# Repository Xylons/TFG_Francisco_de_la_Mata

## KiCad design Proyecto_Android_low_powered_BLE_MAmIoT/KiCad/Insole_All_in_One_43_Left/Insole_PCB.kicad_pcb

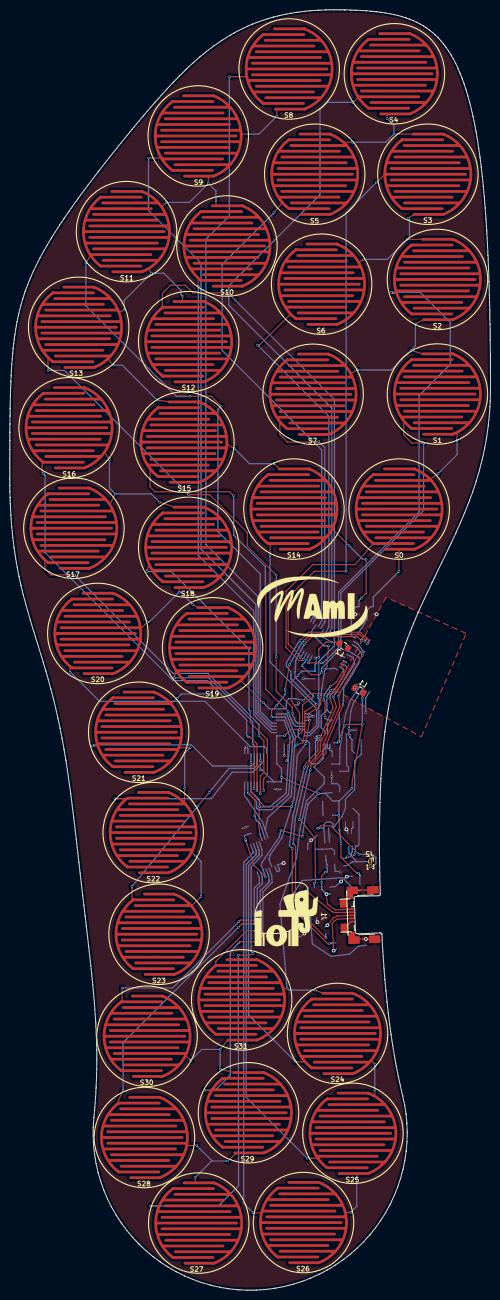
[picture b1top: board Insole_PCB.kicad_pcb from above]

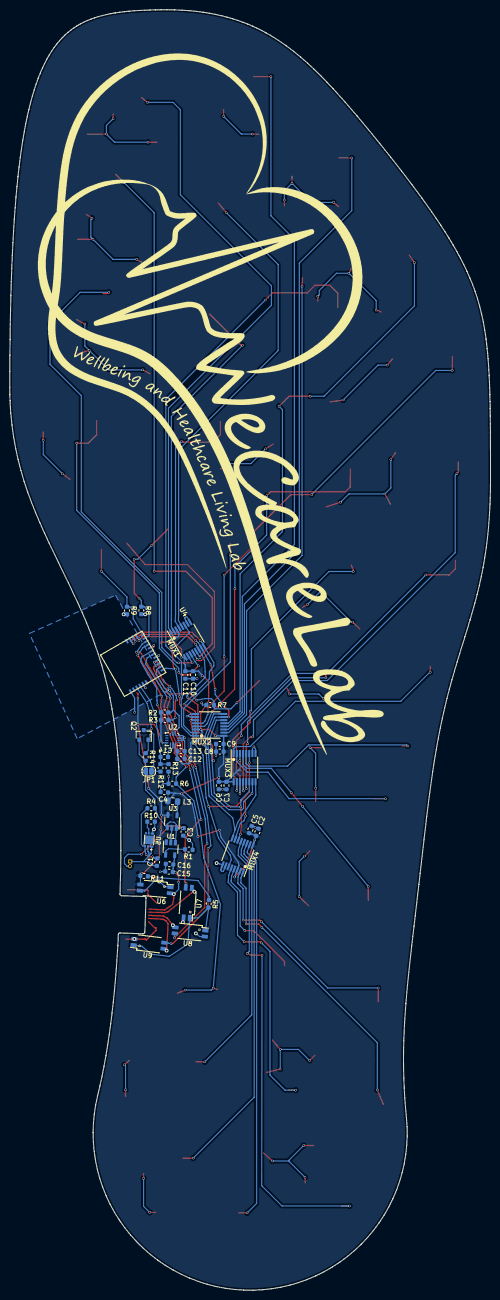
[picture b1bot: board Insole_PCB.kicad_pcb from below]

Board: 2 copper layers, 100.5 x 267.7 mm, 82 parts (46 on the bottom side), 65 nets.

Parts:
C1, C5, C7, C9, C11, C13, C14, C16: 0.1uF; C_0603_1608Metric
C2, C6, C8, C10, C12, C15: 1uF; C_0603_1608Metric
C3: 4.7uF; C_0603_1608Metric
C4: 10uF; C_0603_1608Metric
J1: Conn_Micro_USB; USB_Micro_CustomV2
J2: 3V7_Battery; PinHeader_1x02_P1.00mm_Vertical
JP1: Jumper_NO_Small; SolderJumper-2_P1.3mm_Open_RoundedPad1.0x1.5mm
L1, L2: 300ohm 100MHz; L_0805_2012Metric_Pad1.15x1.40mm_HandSolder
L3: 1uH; L_0805_2012Metric_Pad1.15x1.40mm_HandSolder
MUX1, MUX2, MUX3, MUX4: CD74HC4051; TSSOP-16_4.4x5mm_P0.65mm
Q2: Q_PMOS_GSD; SOT-23
R1, R2, R3, R6, R7, R8, R9, R12, R13: 10k; R_0603_1608Metric
R4: 390 ohm; R_0603_1608Metric
R5: 0-1k; R_0603_1608Metric
R10: 2.7k; R_0603_1608Metric
R11: 100-500 ohm; R_0603_1608Metric
R14: 100k; R_0603_1608Metric
S0, S1, S2, S3, S4, S5, S6, S7, S8, S9, S10, S11, S12, S13, S14, S15, S16, S17, S18, S19, S20, S21, S22, S23, S24, S25, S26, S27, S28, S29, S30, S31: FSR; FSR_Circle_9mm
U1: STC4054-4.2; TSOT-23-5
U2: ISM330DLC; Bosch_LGA-14_3x2.5mm_P0.5mm
U3: ADP2108AUJ-3.3; TSOT-23-5
U4: CYBLE-222014-01
U5: AP9211SA-AN-HAC-7; AP9211SAACHAC7
U6, U7, U8, U9: TCMT1100; SOP-4_4.4x2.8mm_P1.27mm

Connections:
+3V3: C2.2, C4.1, C5.2, C6.2, C7.2, C8.2, C9.2, C10.2, C11.2, C12.2, C13.2, L1.1, L2.1, L3.2, MUX1.3, MUX1.16, MUX2.3, MUX2.16, MUX3.3, MUX3.16, MUX4.3, MUX4.16, R2.1, R3.1, R11.2, U2.5, U2.8, U3.4, U6.4
+5V: C15.2, C16.2, J1.1, U1.4, U6.2
+BATT: C3.2, J2.2, JP1.2, Q2.2, R4.1, R14.1, U1.3, U3.1, U3.3
-BATT: C1.2, J2.1, U5.1, U5.2
/MUX_E: MUX1.6, MUX2.6, MUX3.6, MUX4.6, U4.7
/S0: MUX1.11, MUX2.11, MUX3.11, MUX4.11, U4.19
/S1: MUX1.10, MUX2.10, MUX3.10, MUX4.10, U4.20
/S2: MUX1.9, MUX2.9, MUX3.9, MUX4.9, U4.21
/U1_A0: MUX1.13, S0.2
/U1_A1: MUX1.14, S1.2
/U1_A2: MUX1.15, S2.2
/U1_A3: MUX1.12, S3.2
/U1_A4: MUX1.1, S4.2
/U1_A5: MUX1.5, S5.2
/U1_A6: MUX1.2, S6.2
/U1_A7: MUX1.4, S7.2
/U1_Data: R9.2, S0.1, S1.1, S2.1, S3.1, S4.1, S5.1, S6.1, S7.1, U4.18
/U2_A0: MUX2.13, S8.2
/U2_A1: MUX2.14, S9.2
/U2_A2: MUX2.15, S10.2
/U2_A3: MUX2.12, S11.2
/U2_A4: MUX2.1, S12.2
/U2_A5: MUX2.5, S13.2
/U2_A6: MUX2.2, S14.2
/U2_A7: MUX2.4, S15.2
/U2_Data: R8.2, S8.1, S9.1, S10.1, S11.1, S12.1, S13.1, S14.1, S15.1, U4.17
/U3_A0: MUX3.13, S16.2
/U3_A1: MUX3.14, S17.2
/U3_A2: MUX3.15, S18.2
/U3_A3: MUX3.12, S19.2
/U3_A4: MUX3.1, S20.2
/U3_A5: MUX3.5, S21.2
/U3_A6: MUX3.2, S22.2
/U3_A7: MUX3.4, S23.2
/U3_Data: R7.2, S16.1, S17.1, S18.1, S19.1, S20.1, S21.1, S22.1, S23.1, U4.16
/U4_A0: MUX4.13, S24.2
/U4_A1: MUX4.14, S25.2
/U4_A2: MUX4.15, S26.2
/U4_A3: MUX4.12, S27.2
/U4_A4: MUX4.1, S28.2
/U4_A5: MUX4.5, S29.2
/U4_A6: MUX4.2, S30.2
/U4_A7: MUX4.4, S31.2
/U4_Data: R6.2, S24.1, S25.1, S26.1, S27.1, S28.1, S29.1, S30.1, S31.1, U4.13
Analog_Batt_Lvl: C14.1, R12.2, R13.1, U4.4
Enable_Batt_Lvl: Q2.1, R14.2, U4.3
GND: C2.1, C3.1, C4.2, C5.1, C6.1, C7.1, C8.1, C9.1, C10.1, C11.1, C12.1, C13.1, C14.2, C15.1, C16.1, J1.5, J1.6, MUX1.7, MUX1.8, MUX2.7, MUX2.8, MUX3.7, MUX3.8, MUX4.7, MUX4.8, R1.2, R6.1, R7.1, R8.1, R9.1, R10.2, R13.2, U1.2, U2.1, U2.2, U2.3, U2.6, U2.7, U3.2, U4.1, U4.11, U5.6, U7.2, U8.2, U9.2
unnamed: C1.1, R4.2, U5.3
unnamed: J1.2, U7.4
unnamed: J1.3, U8.4
unnamed: J1.4, U9.4
unnamed: JP1.1, Q2.3, R12.1
unnamed: L1.2, U4.5
unnamed: L2.2, U4.14
unnamed: L3.1, U3.5
unnamed: R1.1, U1.5
unnamed: R2.2, U2.14, U4.9
unnamed: R3.2, U2.13, U4.10
unnamed: R5.1, U7.1, U8.1, U9.1
unnamed: R5.2, U6.3
unnamed: R10.1, U5.5
unnamed: R11.1, U6.1
P0.6: U4.12, U8.3
P0.7: U4.8, U9.3
XRES: U4.15, U7.3

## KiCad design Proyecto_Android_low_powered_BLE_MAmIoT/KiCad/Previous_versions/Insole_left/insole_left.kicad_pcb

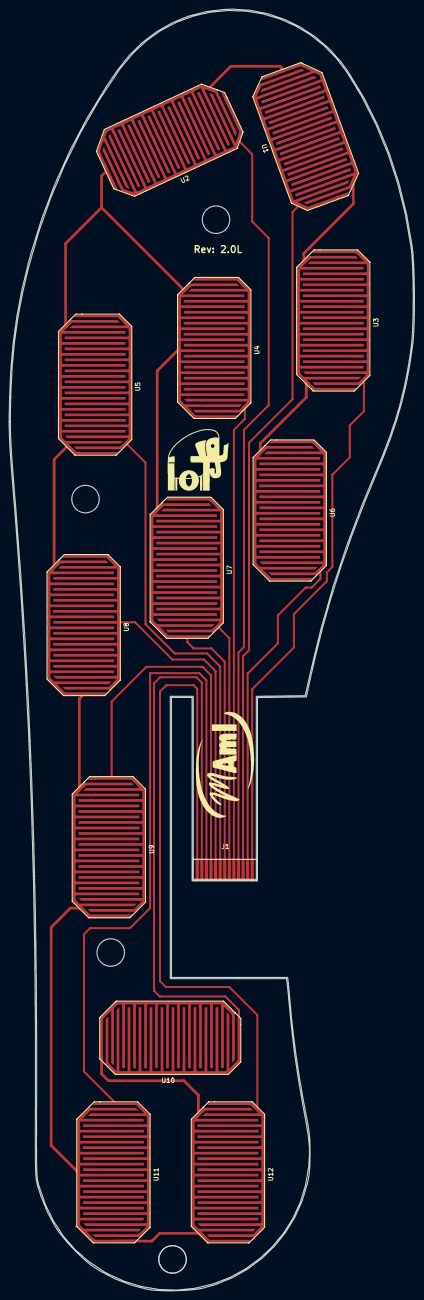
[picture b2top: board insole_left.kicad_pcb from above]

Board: 2 copper layers, 88.5 x 279.8 mm, 13 parts (0 on the bottom side), 13 nets.

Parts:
J1: CONN_01X13; Conn_FPC_1mm
U1, U2, U3, U4, U5, U6, U7, U8, U9, U10, U11, U12: FSR; FSR15x30mm

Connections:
unnamed: J1.1, U12.2
unnamed: J1.2, U10.2
unnamed: J1.3, U11.2
unnamed: J1.4, U9.2
unnamed: J1.5, U8.2
unnamed: J1.6, U5.2
unnamed: J1.7, U1.1, U2.1, U3.1, U4.1, U5.1, U6.1, U7.1, U8.1, U9.1, U10.1, U11.1, U12.1
unnamed: J1.8, U7.2
unnamed: J1.9, U4.2
unnamed: J1.10, U2.2
unnamed: J1.11, U1.2
unnamed: J1.12, U6.2
unnamed: J1.13, U3.2

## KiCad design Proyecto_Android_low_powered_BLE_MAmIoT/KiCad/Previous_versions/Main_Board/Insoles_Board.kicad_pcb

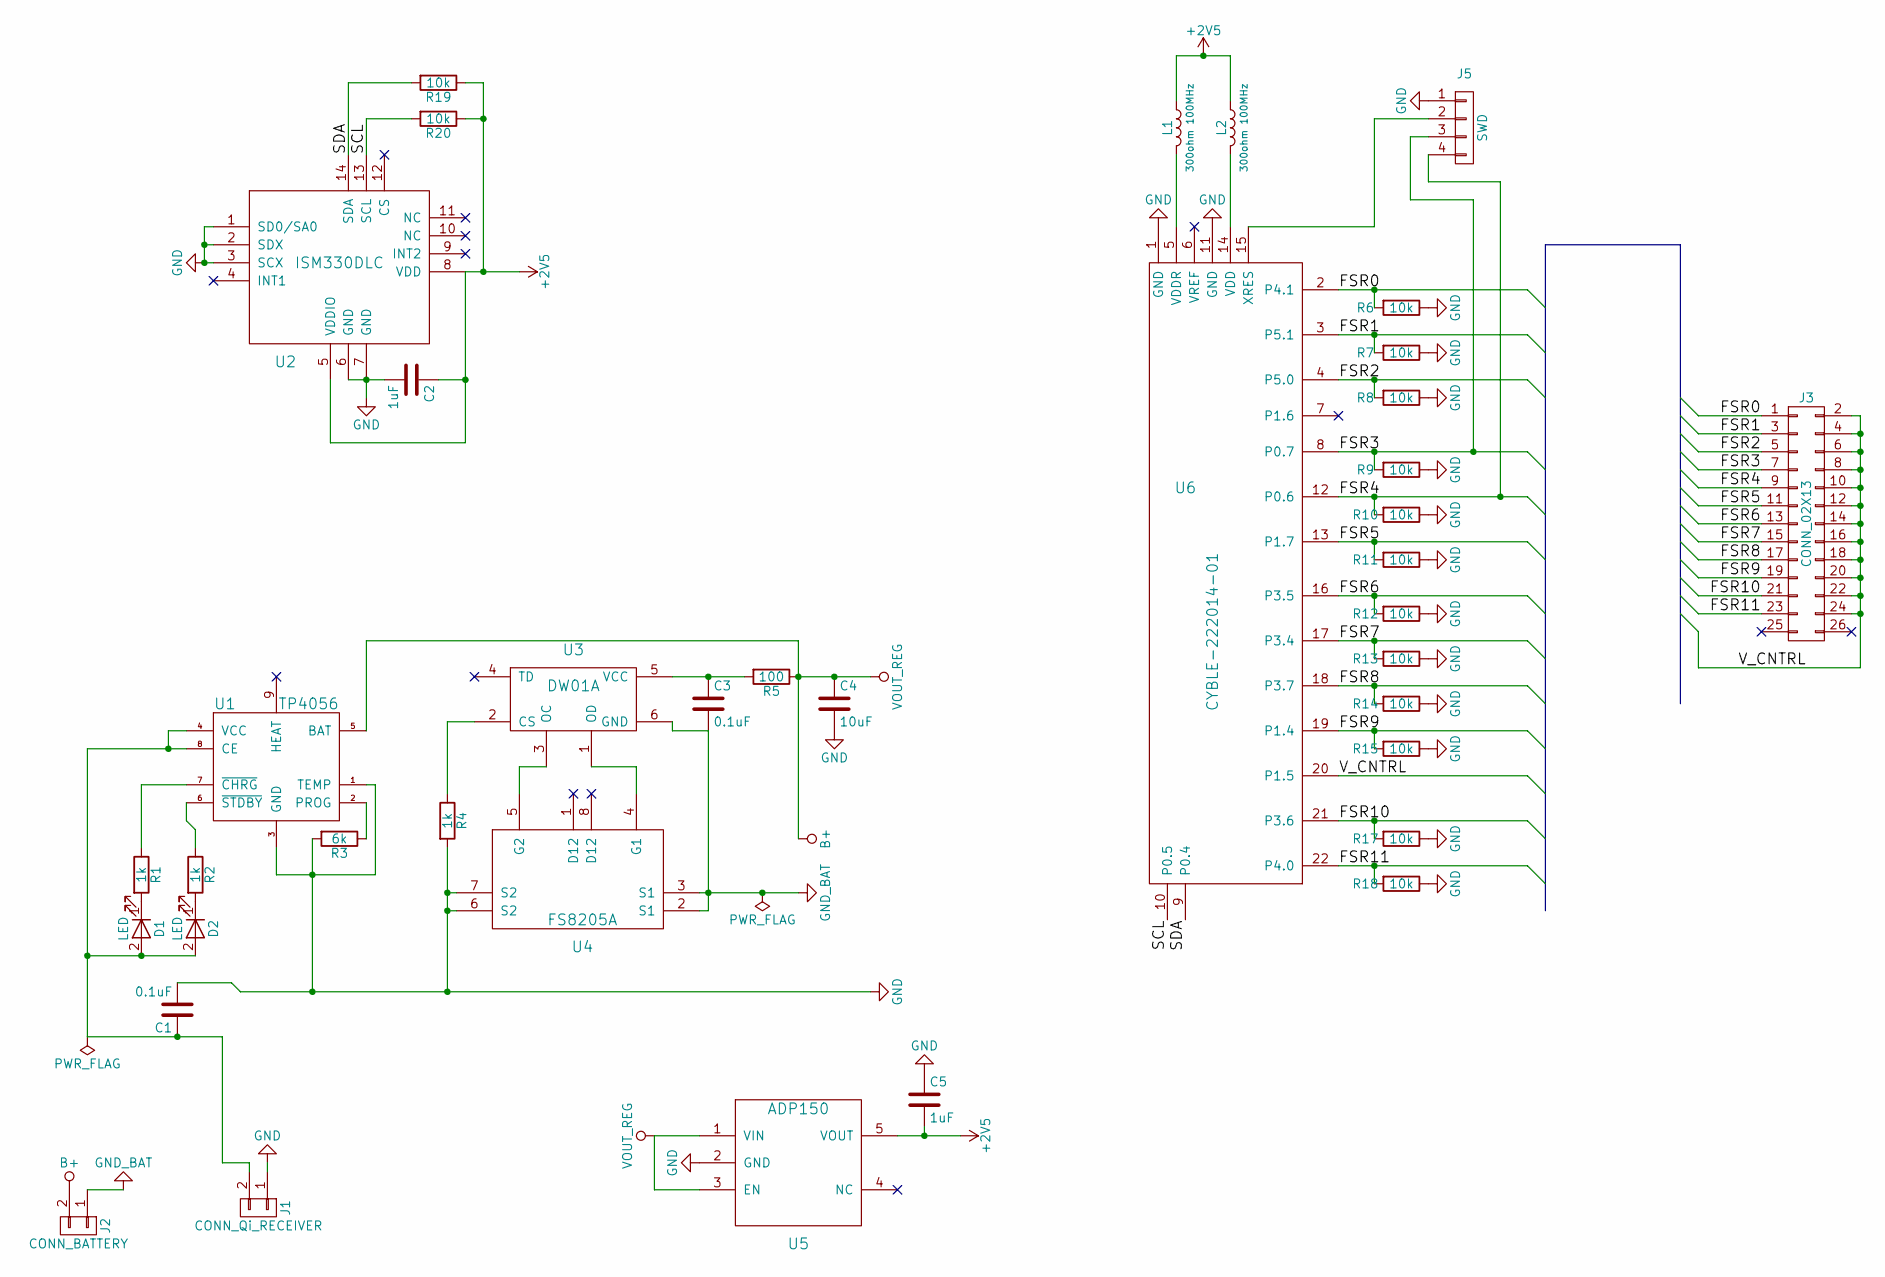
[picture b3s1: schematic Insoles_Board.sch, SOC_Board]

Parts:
C1, C3: 0.1uF; C_0603
C2, C5: 1uF; C_0603
C4: 10uF; C_0603
D1, D2: LED; LED_1206
J1: CONN_Qi_RECEIVER; GS2
J2: CONN_BATTERY; GS2
J3: CONN_02X13; Socket_Strip_Straight_2x13_Pitch1.27mm_SMD
J5: SWD; Hirose_DF13-04P-1.25DS_04x1.25mm_Angled
L1, L2: 300ohm 100MHz; L_0805
R1, R2, R4: 1k; R_0603
R3: 6k; R_0603
R5: 100; R_0603
R6, R7, R8, R9, R10, R11, R12, R13, R14, R15, R17, R18, R19, R20: 10k; R_0603
U1: TP4056; Diodes_PSOP-8
U2: ISM330DLC; Bosch_LGA-14_3x2.5mm_Pitch0.5mm
U3: DW01A; SOT-23-6_Handsoldering
U4: FS8205A; TSSOP-8_4.4x3mm_Pitch0.65mm
U5: ADP150; SOT-23-5_HandSoldering
U6: CYBLE-222014-01; CYBLE-222014-00

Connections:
+2V5: C2.1, C5.2, L1.1, L2.1, R19.1, R20.1, U2.5 (VDDIO), U2.8 (VDD), U5.5 (VOUT)
/FSR0: J3.1, R6.2, U6.2 (P4.1)
/FSR1: J3.3, R7.2, U6.3 (P5.1)
/FSR2: J3.5, R8.2, U6.4 (P5.0)
/FSR3: J3.7, J5.3, R9.2, U6.8 (P0.7)
/FSR4: J3.9, J5.4, R10.2, U6.12 (P0.6)
/FSR5: J3.11, R11.2, U6.13 (P1.7)
/FSR6: J3.13, R12.2, U6.16 (P3.5)
/FSR7: J3.15, R13.2, U6.17 (P3.4)
/FSR8: J3.17, R14.2, U6.18 (P3.7)
/FSR9: J3.19, R15.2, U6.19 (P1.4)
/FSR10: J3.21, R17.2, U6.21 (P3.6)
/FSR11: J3.23, R18.2, U6.22 (P4.0)
/SCL: R20.2, U2.13 (SCL), U6.10 (P0.5)
/SDA: R19.2, U2.14 (SDA), U6.9 (P0.4)
/V_CNTRL: J3.2, J3.4, J3.6, J3.8, J3.10, J3.12, J3.14, J3.16, J3.18, J3.20, J3.22, J3.24, U6.20 (P1.5)
B+: C4.1, J2.2, R5.1, U1.5 (BAT), U5.1 (VIN), U5.3 (EN)
GND: C1.2, C2.2, C4.2, C5.1, J1.1, J5.1, R3.2, R4.2, R6.1, R7.1, R8.1, R9.1, R10.1, R11.1, R12.1, R13.1, R14.1, R15.1, R17.1, R18.1, U1.1 (TEMP), U1.3 (GND), U2.1 (SD0/SA0), U2.2 (SDX), U2.3 (SCX), U2.6 (GND), U2.7 (GND), U4.6 (S2), U4.7 (S2), U5.2 (GND), U6.1 (GND), U6.11 (GND)
GND_BAT: C3.2, J2.1, U3.6 (GND), U4.2 (S1), U4.3 (S1)
unnamed: C1.1, D1.2 (A), D2.2 (A), J1.2, U1.4 (VCC), U1.8 (CE)
unnamed: C3.1, R5.2, U3.5 (VCC)
unnamed: D1.1 (K), R1.2
unnamed: D2.1 (K), R2.2
unnamed: J5.2, U6.15 (XRES)
unnamed: L1.2, U6.5 (VDDR)
unnamed: L2.2, U6.14 (VDD)
unnamed: R1.1, U1.7 (~CHRG)
unnamed: R2.1, U1.6 (~STDBY)
unnamed: R3.1, U1.2 (PROG)
unnamed: R4.1, U3.2 (CS)
unnamed: U3.1 (OD), U4.4 (G1)
unnamed: U3.3 (OC), U4.5 (G2)

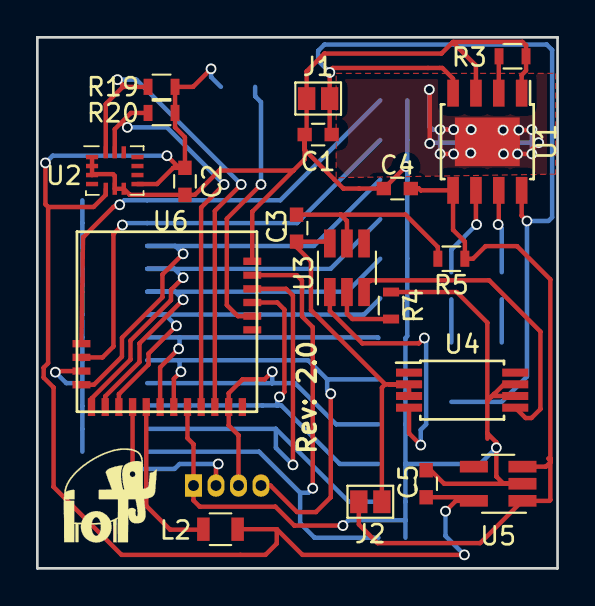
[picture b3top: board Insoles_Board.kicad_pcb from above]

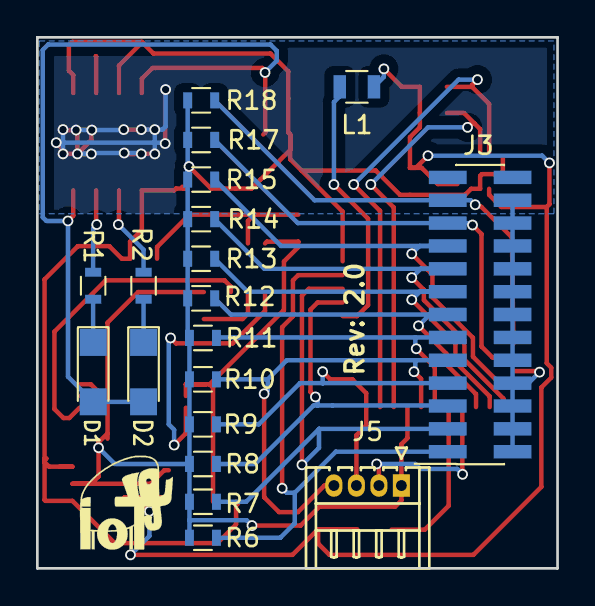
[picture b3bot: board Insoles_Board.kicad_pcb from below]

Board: 2 copper layers, 28.9 x 29.5 mm, 38 parts (19 on the bottom side), 32 nets.
